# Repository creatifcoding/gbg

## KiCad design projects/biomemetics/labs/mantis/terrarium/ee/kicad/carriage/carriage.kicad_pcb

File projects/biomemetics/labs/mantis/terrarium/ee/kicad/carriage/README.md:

# Mantis EE-03 carriage (issue 25)

Theoretical / `UNVERIFIED`. Not a shop release.

Complete B50+B27 12-net channel. Untethered. No CSI on pogos.

S1/S2/Q1 are placed and stitched. Dual-channel Q1, discharge, and isolation
remain #24. This board does not rewrite that truth table.

Regenerate with `python3 ../../../simulations/electrical/channel/tools/generate_kicad.py`.

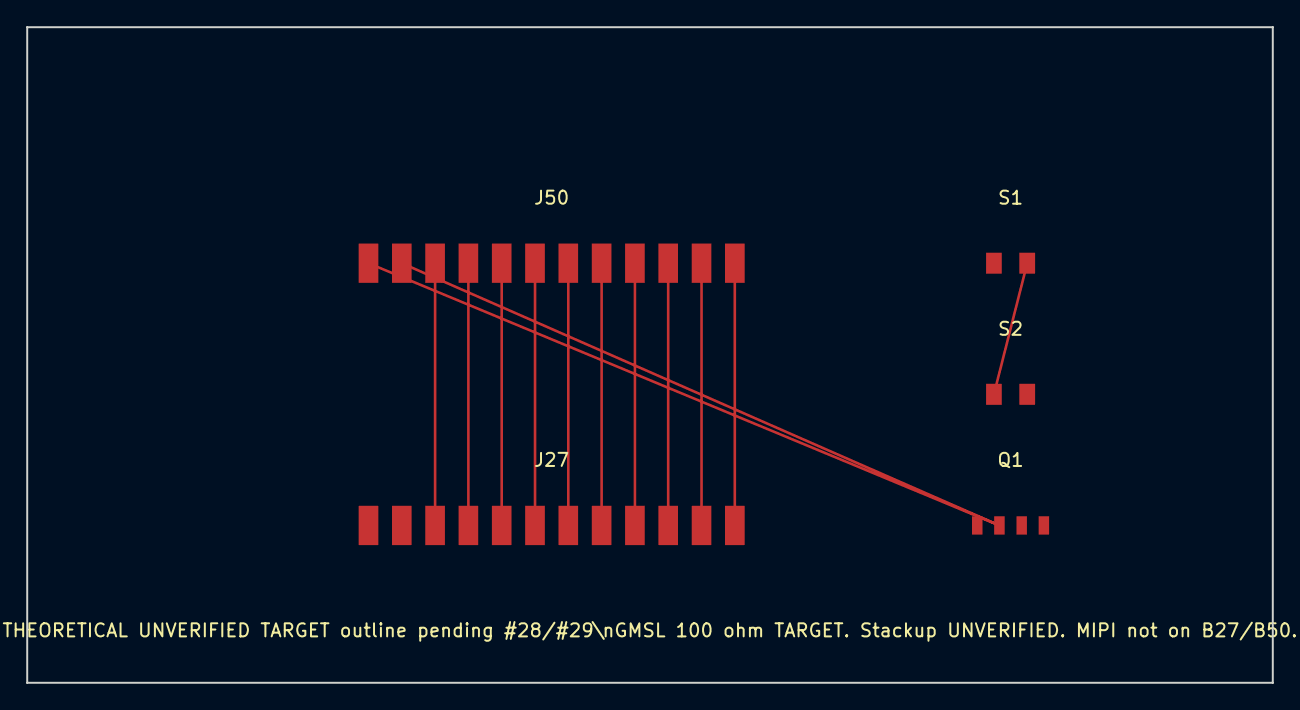
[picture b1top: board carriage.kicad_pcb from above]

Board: 2 copper layers, 95.0 x 50.0 mm, 5 parts (0 on the bottom side), 11 nets.

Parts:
J27: B27_RAIL_12NET_TARGET-2.54mm_UNVERIFIED-series
J50: B50_BINDER_12NET_UNVERIFIED-series
Q1: Q1_LOADSWITCH_UNVERIFIED
S1: S1_NO_SWITCH_UNVERIFIED
S2: S2_NO_SWITCH_UNVERIFIED

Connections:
FAULT_N: J27.P08, J50.C08
GMSL_N: J27.P11, J50.C11
GMSL_P: J27.P10, J50.C10
GND_A: J27.P03, J50.C03
GND_B: J27.P04, J50.C04
HSGND: J27.P09, J27.P12, J50.C09, J50.C12
INTERLOCK_MID: S1.2, S2.1
SCL: J27.P06, J50.C06
SDA: J27.P05, J50.C05
UID: J27.P07, J50.C07
V_BRANCH: J50.C01, J50.C02, Q1.2

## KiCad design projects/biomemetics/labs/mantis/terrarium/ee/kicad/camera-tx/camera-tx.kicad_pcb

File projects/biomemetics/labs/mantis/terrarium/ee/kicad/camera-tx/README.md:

# Mantis EE-03 camera-tx (issue 25)

Theoretical / `UNVERIFIED`. Not a shop release.

Tracks #25 only. Does not implement #18. Does not touch PR 12. Does not rewrite
the #23 library or #24 power-control.

## Locks

- Untethered. No trailing cable.
- Raw MIPI is local to IMX519 and MAX96717.
- Serialized GMSL only on B50 C09–C12 (HSGND, GMSL+, GMSL-, HSGND).
- Video-while-rolling is out of v1.
- IMX519 SKU, MAX96717 suffix/pad map, and B50 series remain UNVERIFIED.

Regenerate:

```text
python3 ../../../simulations/electrical/channel/tools/generate_kicad.py
```

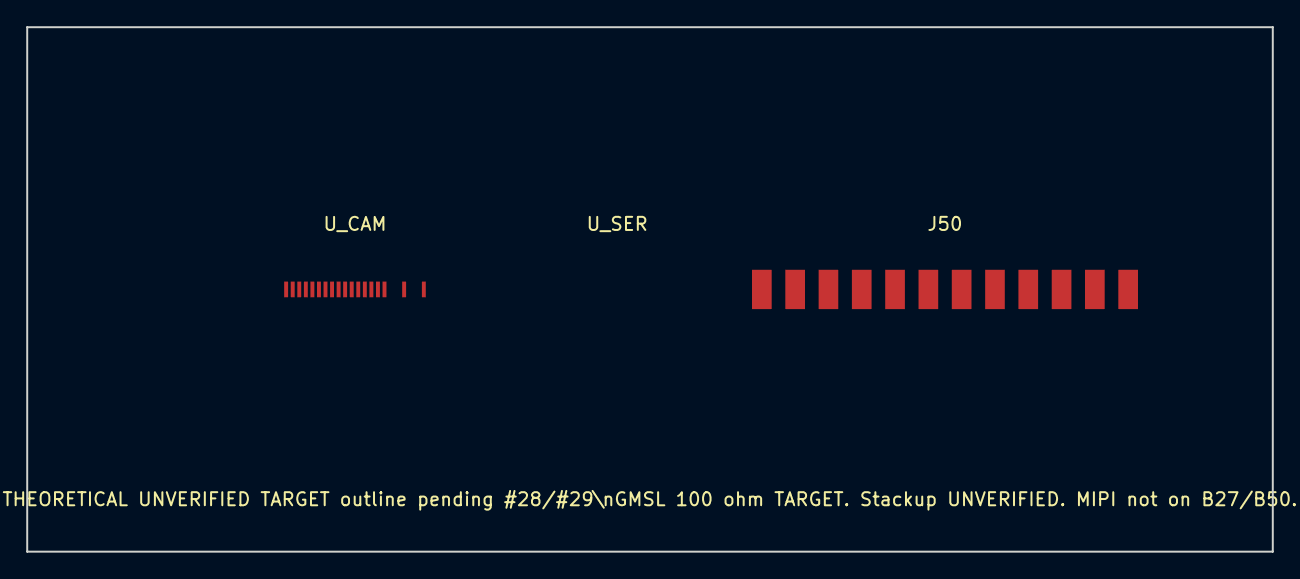
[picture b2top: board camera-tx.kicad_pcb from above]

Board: 2 copper layers, 95.0 x 40.0 mm, 3 parts (0 on the bottom side), 3 nets, no tracks yet.

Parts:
J50: B50_BINDER_12NET_UNVERIFIED-series
U_CAM: FPC-22_0.5mm_UNVERIFIED-MPN
U_SER: MAX96717_PACKAGE_UNVERIFIED

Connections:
GND: U_CAM.1, U_CAM.4, U_CAM.7, U_CAM.10, U_CAM.13, U_CAM.16, U_CAM.19
HSGND: J50.C09, J50.C12
V_BRANCH: J50.C01, J50.C02

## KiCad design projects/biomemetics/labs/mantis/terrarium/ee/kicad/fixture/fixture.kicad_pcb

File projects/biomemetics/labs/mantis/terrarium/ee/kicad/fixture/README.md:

# Mantis EE-04 characterization fixture (issue 26)

Theoretical / `PROTO-FAB DRAFT` / **UNQUALIFIED**. Not a shop release.

`LAB COUPON — CONCEPT VALIDATION — NOT FOR ANIMAL USE`

Tracks #26 only. Does not implement #18. Does not touch PR 12 / SpecimenDB.
Does not rewrite the #23 library or contracts. Does not recreate #24
power-control or #25 camera-tx / carriage / rail-rx (absent on this base).

## Provenance

Reconstituted onto `feat/mantis-biomemetics-lab` @ `6feb3a4a` from closed PR 40
/ `cursor/mantis-ee-26-proto-fab-376a` @ `a9918b32`. Coupon facts (structures,
nets, silk, procedures) copied and adapted; board trees from PR 39 are not on
this base and are not rebuilt. #24/#25 net names are frozen from that source.

## Locks

- Untethered. No trailing cable.
- Raw MIPI is local to SerDes courtyard envelopes. It is not on B50/B27/B19.
- Serialized GMSL only on C09–C12 / P09–P12 (HSGND, GMSL+, GMSL−, HSGND).
- Video-while-rolling is out of v1.
- P08 is diagnostic only.
- No invented MPNs. Missing parts stay `UNVERIFIED` and DNP.
- This coupon does not claim measured SI or PI.
- Human approval is required before ordering, assembly, energization, fault
  injection, or ESD testing.

## Complete coupon (not a decorative subset)

| Sheet | Structure |
| --- | --- |
| `01-cal-2xthru-osl` | 2x-thru B50, 2x-thru B27, open/short/load |
| `02-ser-launch-refplane` | MAX96717 courtyard refplane + B50 launch |
| `03-b50-only` | keyed B50 plug/receptacle, full 12-net |
| `04-carriage-route` | B50 → B27 carriage route, adjacent P01–P08 |
| `05-b27-b19` | B27 + B19 lands, compression note, P09/P12 returns |
| `06-rx-launch-refplane` | MAX96724 courtyard refplane + indexed B27 |
| `07-full-channel` | ser → B50 → carriage → B27 → B19 → rx |
| `08-power-s1s2q1-fault` | AON, S1/S2, Q1A/Q1B, discharge, ISO, probes, faults |

Active-device channel pins are replaced by courtyard reference planes because
the #23 pad maps are UNVERIFIED. Intervening 12-net geometry is not simplified.

## Regenerate

```text
python3 tools/generate_project.py
python3 tools/check_locks.py
```

`kicad-cli` is absent in this runtime. ERC/DRC/Gerber are listed waivers, same
gap as EE-01. Jobsets live under `ee/fab/prototype/jobsets/` and are
planning-only until a pinned KiCad/fabricator path exists. #27 stays held.

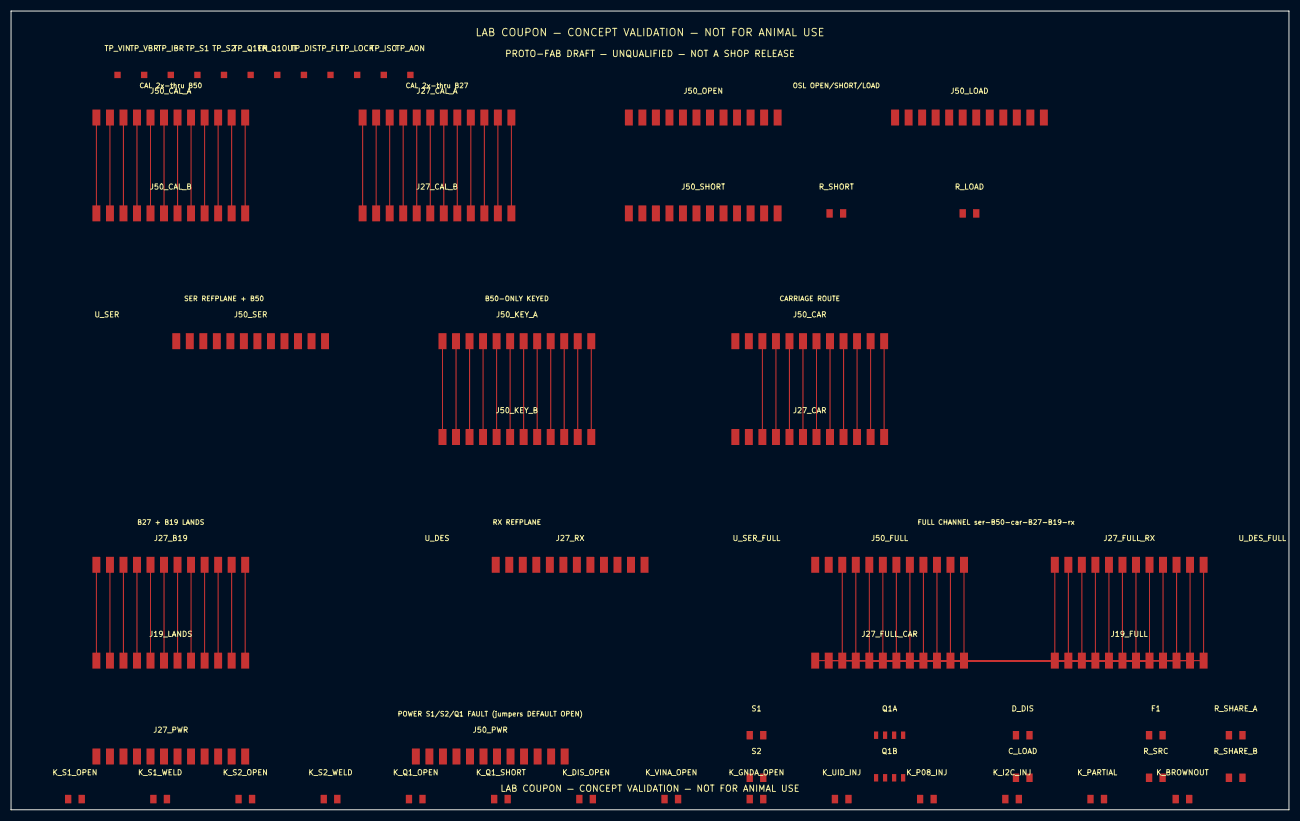
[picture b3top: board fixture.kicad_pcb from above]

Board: 2 copper layers, 240.0 x 150.0 mm, 63 parts (0 on the bottom side), 101 nets.

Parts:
C_LOAD: C_LOAD_UNVERIFIED
D_DIS: DISCHARGE_UNVERIFIED
F1: F1_UNVERIFIED
J19_FULL, J19_LANDS, J27_B19, J27_CAL_A, J27_CAL_B, J27_CAR, J27_FULL_CAR, J27_FULL_RX, J27_PWR, J27_RX: B27_RAIL_12NET_TARGET-2.54mm_UNVERIFIED-series
J50_CAL_A, J50_CAL_B, J50_CAR, J50_FULL, J50_KEY_A, J50_KEY_B, J50_LOAD, J50_OPEN, J50_PWR, J50_SER, J50_SHORT: B50_BINDER_12NET_UNVERIFIED-series
K_BROWNOUT: JMP_FAULT_UNVERIFIED
K_DIS_OPEN: JMP_FAULT_UNVERIFIED
K_GNDA_OPEN: JMP_FAULT_UNVERIFIED
K_I2C_INJ: JMP_FAULT_UNVERIFIED
K_P08_INJ: JMP_FAULT_UNVERIFIED
K_PARTIAL: JMP_FAULT_UNVERIFIED
K_Q1_OPEN, K_Q1_SHORT: JMP_FAULT_UNVERIFIED
K_S1_OPEN, K_S1_WELD, K_S2_OPEN, K_S2_WELD: JMP_FAULT_UNVERIFIED
K_UID_INJ: JMP_FAULT_UNVERIFIED
K_VINA_OPEN: JMP_FAULT_UNVERIFIED
Q1A, Q1B: Q1_LOADSWITCH_UNVERIFIED
R_LOAD: R_UNVERIFIED
R_SHARE_A: R_UNVERIFIED
R_SHARE_B: R_UNVERIFIED
R_SHORT: R_UNVERIFIED
R_SRC: R_SRC_UNVERIFIED
S1: S1_NO_SWITCH_UNVERIFIED
S2: S2_NO_SWITCH_UNVERIFIED
TP_AON: TP_UNVERIFIED
TP_DIS: TP_UNVERIFIED
TP_FLT: TP_UNVERIFIED
TP_IBR: TP_UNVERIFIED
TP_ISO: TP_UNVERIFIED
TP_LOCK: TP_UNVERIFIED
TP_Q1EN, TP_Q1OUT: TP_UNVERIFIED
TP_S1, TP_S2: TP_UNVERIFIED
TP_VBR: TP_UNVERIFIED
TP_VIN: TP_UNVERIFIED
U_DES: MAX96724_PACKAGE_UNVERIFIED
U_DES_FULL: MAX96724_PACKAGE_UNVERIFIED
U_SER: MAX96717_PACKAGE_UNVERIFIED
U_SER_FULL: MAX96717_PACKAGE_UNVERIFIED

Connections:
B19_FAULT_N: J19_LANDS.P08, J27_B19.P08
B19_GMSL_N: J19_LANDS.P11, J27_B19.P11
B19_GMSL_P: J19_LANDS.P10, J27_B19.P10
B19_GND_A: J19_LANDS.P03, J27_B19.P03
B19_GND_B: J19_LANDS.P04, J27_B19.P04
B19_HSGND: J19_LANDS.P09, J19_LANDS.P12, J27_B19.P09, J27_B19.P12
B19_SCL: J19_LANDS.P06, J27_B19.P06
B19_SDA: J19_LANDS.P05, J27_B19.P05
B19_UID: J19_LANDS.P07, J27_B19.P07
B19_VIN_A: J19_LANDS.P01, J27_B19.P01
B19_VIN_B: J19_LANDS.P02, J27_B19.P02
B50ONLY_FAULT_N: J50_KEY_A.C08, J50_KEY_B.C08
B50ONLY_GMSL_N: J50_KEY_A.C11, J50_KEY_B.C11
B50ONLY_GMSL_P: J50_KEY_A.C10, J50_KEY_B.C10
B50ONLY_GND_A: J50_KEY_A.C03, J50_KEY_B.C03
B50ONLY_GND_B: J50_KEY_A.C04, J50_KEY_B.C04
B50ONLY_HSGND: J50_KEY_A.C09, J50_KEY_A.C12, J50_KEY_B.C09, J50_KEY_B.C12
B50ONLY_SCL: J50_KEY_A.C06, J50_KEY_B.C06
B50ONLY_SDA: J50_KEY_A.C05, J50_KEY_B.C05
B50ONLY_UID: J50_KEY_A.C07, J50_KEY_B.C07
B50ONLY_V_BRANCH: J50_KEY_A.C01, J50_KEY_A.C02, J50_KEY_B.C01, J50_KEY_B.C02
CAL27_FAULT_N: J27_CAL_A.P08, J27_CAL_B.P08
CAL27_GMSL_N: J27_CAL_A.P11, J27_CAL_B.P11
CAL27_GMSL_P: J27_CAL_A.P10, J27_CAL_B.P10
CAL27_GND_A: J27_CAL_A.P03, J27_CAL_B.P03
CAL27_GND_B: J27_CAL_A.P04, J27_CAL_B.P04
CAL27_HSGND: J27_CAL_A.P09, J27_CAL_A.P12, J27_CAL_B.P09, J27_CAL_B.P12
CAL27_SCL: J27_CAL_A.P06, J27_CAL_B.P06
CAL27_SDA: J27_CAL_A.P05, J27_CAL_B.P05
CAL27_UID: J27_CAL_A.P07, J27_CAL_B.P07
CAL27_VIN_A: J27_CAL_A.P01, J27_CAL_B.P01
CAL27_VIN_B: J27_CAL_A.P02, J27_CAL_B.P02
CAL50_FAULT_N: J50_CAL_A.C08, J50_CAL_B.C08
CAL50_GMSL_N: J50_CAL_A.C11, J50_CAL_B.C11
CAL50_GMSL_P: J50_CAL_A.C10, J50_CAL_B.C10
CAL50_GND_A: J50_CAL_A.C03, J50_CAL_B.C03
CAL50_GND_B: J50_CAL_A.C04, J50_CAL_B.C04
CAL50_HSGND: J50_CAL_A.C09, J50_CAL_A.C12, J50_CAL_B.C09, J50_CAL_B.C12
CAL50_SCL: J50_CAL_A.C06, J50_CAL_B.C06
CAL50_SDA: J50_CAL_A.C05, J50_CAL_B.C05
CAL50_UID: J50_CAL_A.C07, J50_CAL_B.C07
CAL50_VIN_A: J50_CAL_A.C01, J50_CAL_B.C01
CAL50_VIN_B: J50_CAL_A.C02, J50_CAL_B.C02
CAR_FAULT_N: J27_CAR.P08, J50_CAR.C08
CAR_GMSL_N: J27_CAR.P11, J50_CAR.C11
CAR_GMSL_P: J27_CAR.P10, J50_CAR.C10
CAR_GND_A: J27_CAR.P03, J50_CAR.C03
CAR_GND_B: J27_CAR.P04, J50_CAR.C04
CAR_HSGND: J27_CAR.P09, J27_CAR.P12, J50_CAR.C09, J50_CAR.C12
CAR_SCL: J27_CAR.P06, J50_CAR.C06
CAR_SDA: J27_CAR.P05, J50_CAR.C05
CAR_UID: J27_CAR.P07, J50_CAR.C07
CAR_V_BRANCH: J50_CAR.C01, J50_CAR.C02
DISCH_SRC: D_DIS.2, K_DIS_OPEN.1
FAULT_N: J27_PWR.P08, J50_PWR.C08, K_P08_INJ.1
FULL_FAULT_N: J19_FULL.P08, J27_FULL_CAR.P08, J27_FULL_RX.P08, J50_FULL.C08
FULL_GMSL_N: J19_FULL.P11, J27_FULL_CAR.P11, J27_FULL_RX.P11, J50_FULL.C11
FULL_GMSL_P: J19_FULL.P10, J27_FULL_CAR.P10, J27_FULL_RX.P10, J50_FULL.C10
FULL_GND_A: J19_FULL.P03, J27_FULL_CAR.P03, J27_FULL_RX.P03, J50_FULL.C03
FULL_GND_B: J19_FULL.P04, J27_FULL_CAR.P04, J27_FULL_RX.P04, J50_FULL.C04
FULL_HSGND: J19_FULL.P09, J19_FULL.P12, J27_FULL_CAR.P09, J27_FULL_CAR.P12, J27_FULL_RX.P09, J27_FULL_RX.P12, J50_FULL.C09, J50_FULL.C12
FULL_SCL: J19_FULL.P06, J27_FULL_CAR.P06, J27_FULL_RX.P06, J50_FULL.C06
FULL_SDA: J19_FULL.P05, J27_FULL_CAR.P05, J27_FULL_RX.P05, J50_FULL.C05
FULL_UID: J19_FULL.P07, J27_FULL_CAR.P07, J27_FULL_RX.P07, J50_FULL.C07
FULL_VIN_A: J19_FULL.P01, J27_FULL_CAR.P01, J27_FULL_RX.P01
FULL_VIN_B: J19_FULL.P02, J27_FULL_CAR.P02, J27_FULL_RX.P02
FULL_V_BRANCH: J50_FULL.C01, J50_FULL.C02
GMSL_N: J27_PWR.P11, J50_PWR.C11
GMSL_P: J27_PWR.P10, J50_PWR.C10
GND: C_LOAD.2, K_DIS_OPEN.2, K_GNDA_OPEN.1, Q1A.4, Q1B.4
GND_A: J27_PWR.P03, J50_PWR.C03, K_GNDA_OPEN.2
GND_B: J27_PWR.P04, J50_PWR.C04
HSGND: J27_PWR.P09, J27_PWR.P12, J50_PWR.C09, J50_PWR.C12
INTERLOCK_MID: K_PARTIAL.2, K_S1_WELD.2, K_S2_OPEN.1, K_S2_WELD.1, S1.2, TP_S1.1
INTERLOCK_OK: K_S2_WELD.2, S2.2, TP_S2.1
OSL_LOAD_GMSL_N: J50_LOAD.C11, R_LOAD.2
OSL_LOAD_GMSL_P: J50_LOAD.C10, R_LOAD.1
OSL_LOAD_HSGND: J50_LOAD.C09, J50_LOAD.C12
OSL_OPEN_HSGND: J50_OPEN.C09, J50_OPEN.C12
OSL_SHORT_GMSL_N: J50_SHORT.C11, R_SHORT.2
OSL_SHORT_GMSL_P: J50_SHORT.C10, R_SHORT.1
OSL_SHORT_HSGND: J50_SHORT.C09, J50_SHORT.C12
Q1A_VIN: K_Q1_OPEN.2, Q1A.1
Q1_EN: Q1A.3, Q1B.3, TP_Q1EN.1
Q1_MID: Q1A.2, Q1B.1, TP_IBR.1
RX_HSGND: J27_RX.P09, J27_RX.P12
S1_COM: K_S1_OPEN.2, S1.1
S2_COM: K_S2_OPEN.2, S2.1
SCL: J27_PWR.P06, J50_PWR.C06
SDA: J27_PWR.P05, J50_PWR.C05, K_I2C_INJ.1
SER_HSGND: J50_SER.C09, J50_SER.C12
SER_V_BRANCH: J50_SER.C01, J50_SER.C02
UID: J27_PWR.P07, J50_PWR.C07, K_UID_INJ.1
VIN_A: J27_PWR.P01, K_VINA_OPEN.2, R_SHARE_A.1
VIN_AON: K_S1_OPEN.1, K_S1_WELD.1, TP_AON.1
VIN_B: J27_PWR.P02, R_SHARE_B.1
VIN_FUSED: F1.2, K_VINA_OPEN.1
VIN_FUSED_PRE: F1.1, R_SRC.2
VIN_RAIL: K_BROWNOUT.1, R_SRC.1, TP_VIN.1
VIN_SHARED: K_Q1_OPEN.1, K_Q1_SHORT.1, R_SHARE_A.2, R_SHARE_B.2
V_BRANCH: C_LOAD.1, D_DIS.1, J50_PWR.C01, J50_PWR.C02, K_Q1_SHORT.2, Q1B.2, TP_Q1OUT.1, TP_VBR.1

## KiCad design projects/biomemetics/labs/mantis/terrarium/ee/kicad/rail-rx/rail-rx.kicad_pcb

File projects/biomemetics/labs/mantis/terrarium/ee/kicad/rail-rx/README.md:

# Mantis EE-03 rail-rx (issue 25)

Theoretical / `UNVERIFIED`. Not a shop release.

Indexed B27 dock, MAX96724 envelope, short local CSI to Tachyon CSI1.
MIPI does not ride B27. MAX96724 suffix/pad map UNVERIFIED.

Regenerate with `python3 ../../../simulations/electrical/channel/tools/generate_kicad.py`.

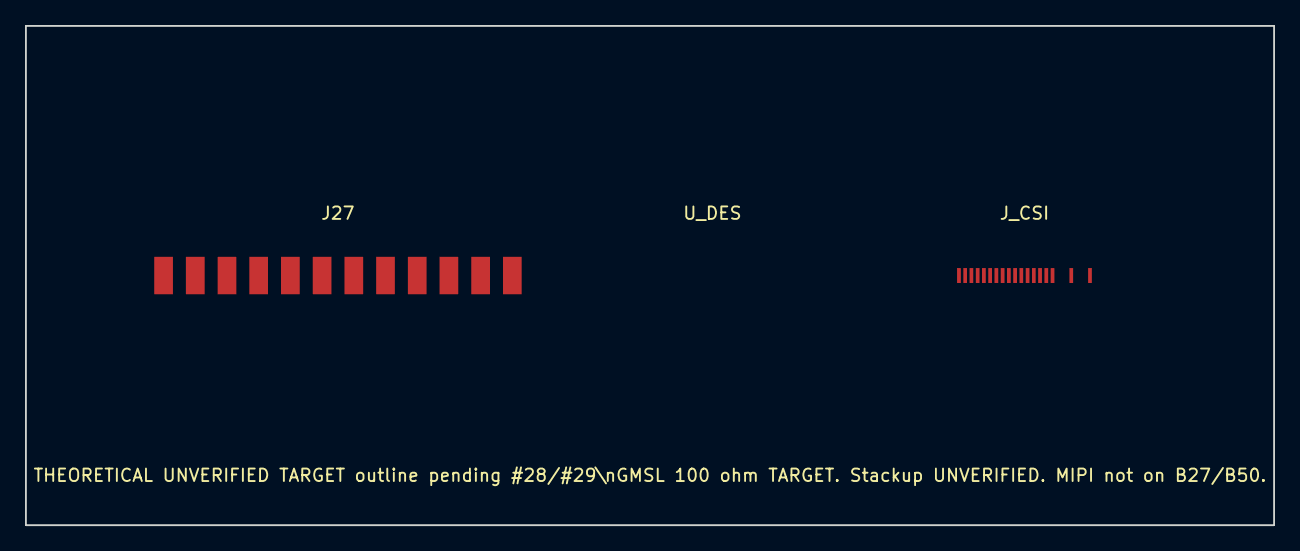
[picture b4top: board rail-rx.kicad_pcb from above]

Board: 2 copper layers, 100.0 x 40.0 mm, 3 parts (0 on the bottom side), 2 nets, no tracks yet.

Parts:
J27: B27_RAIL_12NET_TARGET-2.54mm_UNVERIFIED-series
J_CSI: FPC-22_0.5mm_UNVERIFIED-MPN
U_DES: MAX96724_PACKAGE_UNVERIFIED

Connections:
GND: J_CSI.1, J_CSI.4, J_CSI.7, J_CSI.10, J_CSI.13, J_CSI.16, J_CSI.19
HSGND: J27.P09, J27.P12

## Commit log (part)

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2026-05-26 refactor(effect-sui): decompose flow runner reconciliation
2026-05-26 docs(effect-sui): record runner reconciliation decomposition
2026-05-26 refactor(effect-sui): decompose query BCS codec helpers
2026-05-26 docs(effect-sui): record query BCS decomposition
2026-05-26 refactor(effect-sui): decompose schema byte helpers
2026-05-26 docs(effect-sui): record byte helper decomposition
2026-05-26 Add Reactor v2 promotion substrate
2026-05-26 refactor(effect-sui): decompose shared object ref decoder
2026-05-26 docs(effect-sui): record shared-ref decoder decomposition
2026-05-26 Promote WorkOrder depends_on Reactor lane
2026-05-26 Promote alarm safety Reactor lane
2026-05-26 Promote structural decommission Reactor lane
2026-05-26 feat(effect-sui): add finality watcher fibers
2026-05-26 docs(effect-sui): record finality watcher fibers
2026-05-26 feat(effect-sui): add typed error topology
2026-05-26 docs(effect-sui): record typed error topology
2026-05-27 Extract IIoT domain graph query services
2026-05-27 feat(effect-sui): normalize typed error causes
2026-05-27 docs(effect-sui): record typed error normalizers
2026-05-27 Promote external device availability Reactor lane
2026-05-27 feat(effect-sui): add diagnostics classification surface
2026-05-27 docs(effect-sui): record diagnostics surface
2026-05-27 Harden Reactor source-claim recovery
2026-05-27 Close out Reactor v2 promotion program
2026-05-27 feat(effect-sui): add move package publish helper
2026-05-27 docs(effect-sui): record move publish helper
2026-05-27 feat(effect-sui): add wallet callback bridge
2026-05-27 docs(effect-sui): record wallet callback bridge
2026-05-27 feat(effect-sui): add runtime fixture scopes
2026-05-27 docs(effect-sui): record runtime fixture scopes
2026-05-27 feat(effect-sui): add reservation persistence hooks
2026-05-27 docs(effect-sui): record reservation persistence
2026-05-27 docs(effect-sui): prepare release candidate notes
2026-05-27 docs(effect-sui): record release prep
2026-05-28 Add industrial agentic platform RFC pack
2026-05-28 Add industrial platform RFC reader generator
2026-05-28 Ground industrial platform RFCs in standards traceability
2026-05-28 Decompose plant ops platform boundaries
2026-05-28 chore(effect-sui): curate Sui localnet and Move tooling
2026-05-28 docs(tmnl): add Effect-Sui development skill
2026-05-28 chore: align workspace effect runtime
2026-05-28 fix: lazy load node sqlite adapter
2026-05-28 chore: remove react grab dev integration
2026-05-28 fix: isolate harness pi extension loading
2026-05-30 chore(global): add .gitattributes provisions for linguist.
2026-06-07 docs(muse): document Muse protocol and ingest path
2026-06-07 feat(muse): add classic BLE packet decoder
2026-06-07 feat(muse): stream decoded BLE samples with keepalive
2026-06-07 feat(muse): add safe control poke utility
2026-06-07 feat(muse): define floating panel event contracts
2026-06-07 fix(stx): align stream state with Legend v3 typings
2026-06-07 feat(muse): add local WebSocket ingest adapter
2026-06-08 Add pi session ledger data model
2026-06-08 Add pi CLI session replay source
2026-06-08 Wire pi sessions through harness runtime
2026-06-08 Fix TMNL dev startup for browser smoke
2026-06-08 feat(muse): add floating log capture panel
2026-06-08 feat(muse): add decoded sample CSV artifact
2026-06-08 feat(muse): add OSC sample fanout
2026-06-08 feat(muse): add first-order capture analyzer
2026-06-08 feat(muse): define controlled session contracts
2026-06-08 docs(muse): document controlled protocol limits
2026-06-08 Add cached pi session metadata source
2026-06-08 Project pi sessions into the drawer state
2026-06-08 Refine session drawer rows and smoke coverage
2026-06-08 Fix harness dev diagnostics quoting
2026-06-08 Harden live session drawer rendering
2026-06-08 fix(muse): align session clock domain with capture timestamps
2026-06-08 docs(muse): define metric pack realization plan
2026-06-08 feat(muse): add metric pack analyzer substrate
2026-06-08 feat(muse): add protocol compliance validator
2026-06-08 feat(muse): validate protocol export metadata
2026-06-08 feat(muse): add transport timing summary metrics
2026-06-08 docs(muse): define transport integrity thresholds
2026-06-08 feat(muse): emit transport integrity reports
2026-06-08 docs(muse): design contact fit proxy gate
